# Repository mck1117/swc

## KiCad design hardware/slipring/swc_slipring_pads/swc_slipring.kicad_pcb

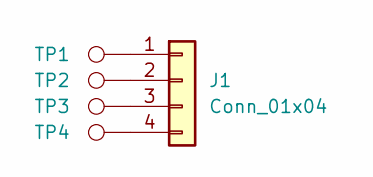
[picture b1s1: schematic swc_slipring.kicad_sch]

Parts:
J1: Conn_01x04; PinSocket_2x02_P2.54mm_Vertical_SMD
TP1, TP2, TP3, TP4: TestPoint; TestPoint_Pad_D3.0mm

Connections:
unnamed: J1.1, TP1.1
unnamed: J1.2, TP2.1
unnamed: J1.3, TP3.1
unnamed: J1.4, TP4.1

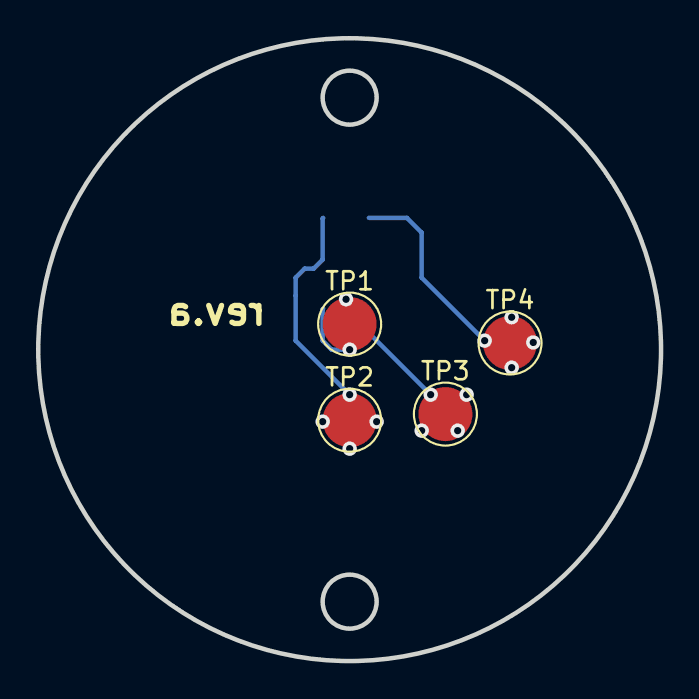
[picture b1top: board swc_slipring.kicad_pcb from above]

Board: 2 copper layers, 34.6 x 34.6 mm, 5 parts (1 on the bottom side), 4 nets.

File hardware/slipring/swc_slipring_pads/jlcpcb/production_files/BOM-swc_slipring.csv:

Comment,Designator,Footprint,LCSC
Conn_01x04,J1,PinSocket_2x02_P2.54mm_Vertical_SMD,
TestPoint,TP4,TestPoint_Pad_D3.0mm,
TestPoint,TP3,TestPoint_Pad_D3.0mm,
TestPoint,TP2,TestPoint_Pad_D3.0mm,
TestPoint,TP1,TestPoint_Pad_D3.0mm,

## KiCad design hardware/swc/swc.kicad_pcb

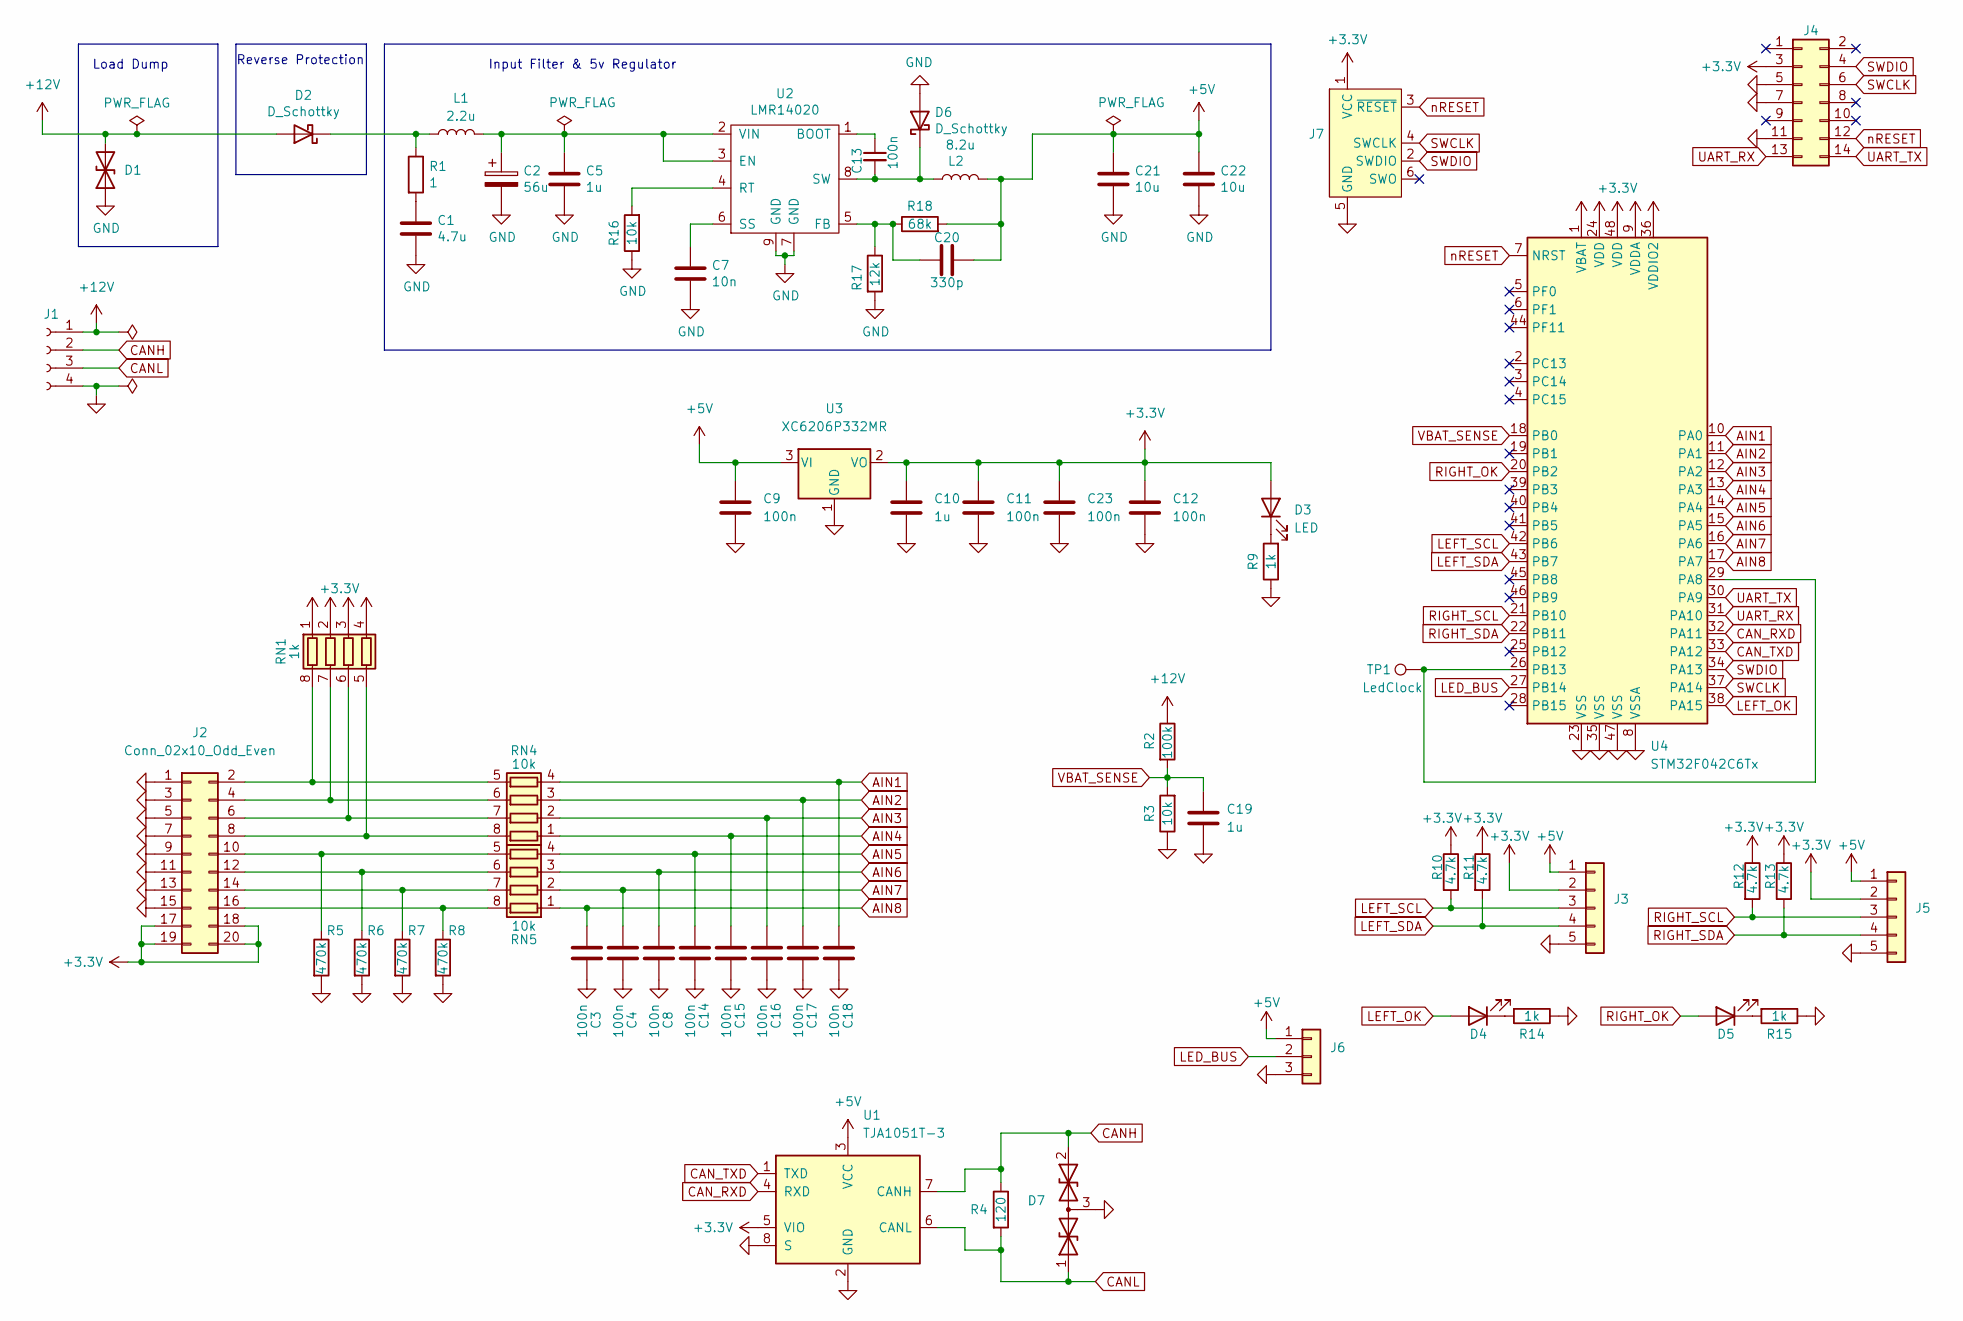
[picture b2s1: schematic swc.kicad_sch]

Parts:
C1: 4.7u; C_0603_1608Metric; LCSC C19666
C2: 56u; CP_Radial_D8.0mm_P3.50mm; LCSC N/A
C3, C4, C8, C9, C11, C12, C13, C14, C15, C16, C17, C18, C23: 100n; C_0603_1608Metric; LCSC C14663
C5, C10, C19: 1u; C_0603_1608Metric; LCSC C15849
C7: 10n; C_0402_1005Metric; LCSC_ext 0
C20: 330p; C_0402_1005Metric; LCSC C13533
C21, C22: 10u; C_1206_3216Metric; LCSC C13585
D1: SMBJ24CA; D_SMB; LCSC C78416
D2, D6: D_Schottky; D_SMA; LCSC C8678
D3, D4, D5: LED; LED_0603_1608Metric; LCSC C72041
D7: PESD1CAN; SOT-323_SC-70; LCSC C152727
J1: Conn_01x04_Female; JST_XH_B4B-XH-A_1x04_P2.50mm_Vertical
J2: Conn_02x10_Odd_Even; PinHeader_2x10_P2.00mm_Vertical
J3, J5: Conn_01x05; JST_XH_B5B-XH-A_1x05_P2.50mm_Vertical
J4: FTSH-107-01-F-DV-K; PinHeader_2x07_P1.27mm_Vertical_SMD
J6: Conn_01x03; JST_XH_B3B-XH-A_1x03_P2.50mm_Vertical
J7: Conn_ARM_SWD_TagConnect_TC2030-NL; Tag-Connect_TC2030-IDC-NL_2x03_P1.27mm_Vertical
L1: 2.2u; L_1210_3225Metric; LCSC C36828
L2: 8.2u; L_Bourns_SRN6045TA
R1: 1; R_0402_1005Metric; LCSC C25086
R2: 100k; R_0603_1608Metric; LCSC C25803
R3, R16: 10k; R_0603_1608Metric; LCSC C25804
R4: 120; R_0805_2012Metric; LCSC C17437
R5, R6, R7, R8: 470k; R_0402_1005Metric
R9, R14, R15: 1k; R_0603_1608Metric; LCSC C21190
R10, R11, R12, R13: 4.7k; R_0603_1608Metric
R17: 12k; R_0402_1005Metric; LCSC C25752
R18: 68k; R_0402_1005Metric; LCSC C36871
RN1: 1k; R_Array_Convex_4x0603
RN4, RN5: 10k; R_Array_Convex_4x0603; LCSC C29718
TP1: LedClock; TestPoint_Pad_1.5x1.5mm
U1: TJA1051T-3; SOIC-8_3.9x4.9mm_P1.27mm; LCSC C38695
U2: LMR14020; SOIC-8-1EP_3.9x4.9mm_P1.27mm_EP2.29x3mm; LCSC C187824
U3: XC6206P332MR; SOT-23; LCSC C5446
U4: STM32F042C6Tx; LQFP-48_7x7mm_P0.5mm; LCSC C88447

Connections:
+3V3: C10.1, C11.1, C12.1, C23.1, D3.2 (A), J2.17, J2.18, J2.19, J2.20, J3.2, J4.3, J5.2, J7.1 (VCC), R10.1, R11.1, R12.1, R13.1, RN1.1 (R1.1), RN1.2 (R2.1), RN1.3 (R3.1), RN1.4 (R4.1), U1.5 (VIO), U3.2 (VO), U4.1 (VBAT), U4.9 (VDDA), U4.24 (VDD), U4.36 (VDDIO2), U4.48 (VDD)
+5V: C9.1, C20.1, C21.1, C22.1, J3.1, J5.1, J6.1, L2.2, R18.2, U1.3 (VCC), U3.3 (VI)
+12V: D1.2 (A2), D2.2 (A), J1.1, R2.1
AIN1: C18.1, RN4.4 (R4.1), U4.10 (PA0)
AIN2: C17.1, RN4.3 (R3.1), U4.11 (PA1)
AIN3: C16.1, RN4.2 (R2.1), U4.12 (PA2)
AIN4: C15.1, RN4.1 (R1.1), U4.13 (PA3)
AIN5: C14.1, RN5.4 (R4.1), U4.14 (PA4)
AIN6: C8.1, RN5.3 (R3.1), U4.15 (PA5)
AIN7: C4.1, RN5.2 (R2.1), U4.16 (PA6)
AIN8: C3.1, RN5.1 (R1.1), U4.17 (PA7)
CANH: D7.2 (A2), J1.2, R4.1, U1.7 (CANH)
CANL: D7.1 (A1), J1.3, R4.2, U1.6 (CANL)
CAN_RXD: U1.4 (RXD), U4.32 (PA11)
CAN_TXD: U1.1 (TXD), U4.33 (PA12)
GND: C1.2, C2.2, C3.2, C4.2, C5.2, C7.2, C8.2, C9.2, C10.2, C11.2, C12.2, C14.2, C15.2, C16.2, C17.2, C18.2, C19.2, C21.2, C22.2, C23.2, D1.1 (A1), D6.2 (A), D7.3 (common), J1.4, J2.1, J2.3, J2.5, J2.7, J2.9, J2.11, J2.13, J2.15, J3.5, J4.5, J4.7, J4.11, J5.5, J6.3, J7.5 (GND), R3.1, R5.2, R6.2, R7.2, R8.2, R9.1, R14.1, R15.1, R16.1, R17.2, U1.2 (GND), U1.8 (S), U2.7 (GND), U2.9 (GND), U3.1 (GND), U4.8 (VSSA), U4.23 (VSS), U4.35 (VSS), U4.47 (VSS)
LED_BUS: J6.2, U4.27 (PB14)
LEFT_OK: D4.2 (A), U4.38 (PA15)
LEFT_SCL: J3.3, R10.2, U4.42 (PB6)
LEFT_SDA: J3.4, R11.2, U4.43 (PB7)
unnamed: C1.1, R1.2
unnamed: C2.1, C5.1, L1.2, U2.2 (VIN), U2.3 (EN)
unnamed: C7.1, U2.6 (SS)
unnamed: C13.1, U2.1 (BOOT)
unnamed: C13.2, D6.1 (K), L2.1, U2.8 (SW)
unnamed: C20.2, R17.1, R18.1, U2.5 (FB)
unnamed: D2.1 (K), L1.1, R1.1
unnamed: D3.1 (K), R9.2
unnamed: D4.1 (K), R14.2
unnamed: D5.1 (K), R15.2
unnamed: J2.2, RN1.8 (R1.2), RN4.5 (R4.2)
unnamed: J2.4, RN1.7 (R2.2), RN4.6 (R3.2)
unnamed: J2.6, RN1.6 (R3.2), RN4.7 (R2.2)
unnamed: J2.8, RN1.5 (R4.2), RN4.8 (R1.2)
unnamed: J2.10, R5.1, RN5.5 (R4.2)
unnamed: J2.12, R6.1, RN5.6 (R3.2)
unnamed: J2.14, R7.1, RN5.7 (R2.2)
unnamed: J2.16, R8.1, RN5.8 (R1.2)
unnamed: R16.2, U2.4 (RT)
unnamed: TP1.1, U4.26 (PB13), U4.29 (PA8)
RIGHT_OK: D5.2 (A), U4.20 (PB2)
RIGHT_SCL: J5.3, R12.2, U4.21 (PB10)
RIGHT_SDA: J5.4, R13.2, U4.22 (PB11)
SWCLK: J4.6, J7.4 (SWCLK), U4.37 (PA14)
SWDIO: J4.4, J7.2 (SWDIO), U4.34 (PA13)
UART_RX: J4.13, U4.31 (PA10)
UART_TX: J4.14, U4.30 (PA9)
VBAT_SENSE: C19.1, R2.2, R3.2, U4.18 (PB0)
nRESET: J4.12, J7.3 (~RESET), U4.7 (NRST)

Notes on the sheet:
Input Filter & 5v Regulator
Load Dump
Reverse Protection

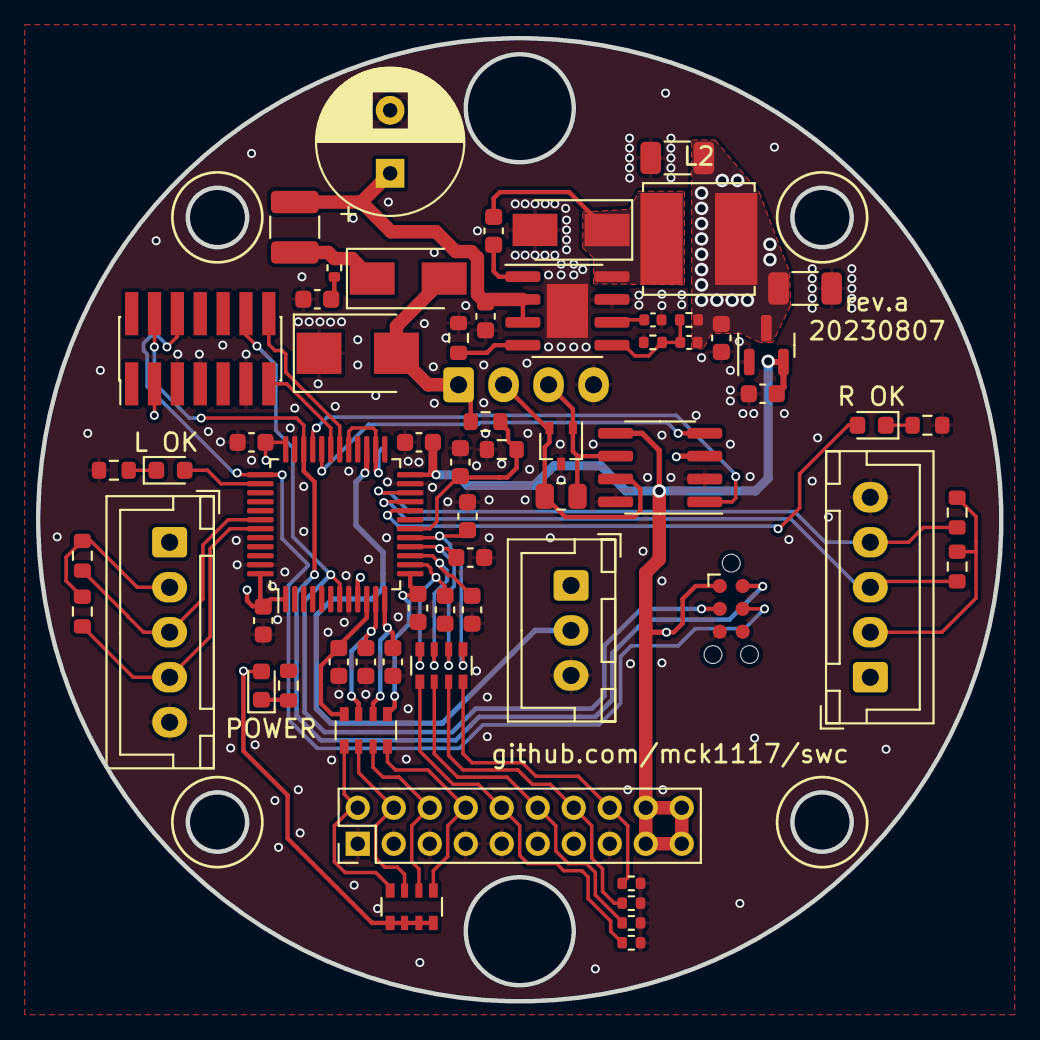
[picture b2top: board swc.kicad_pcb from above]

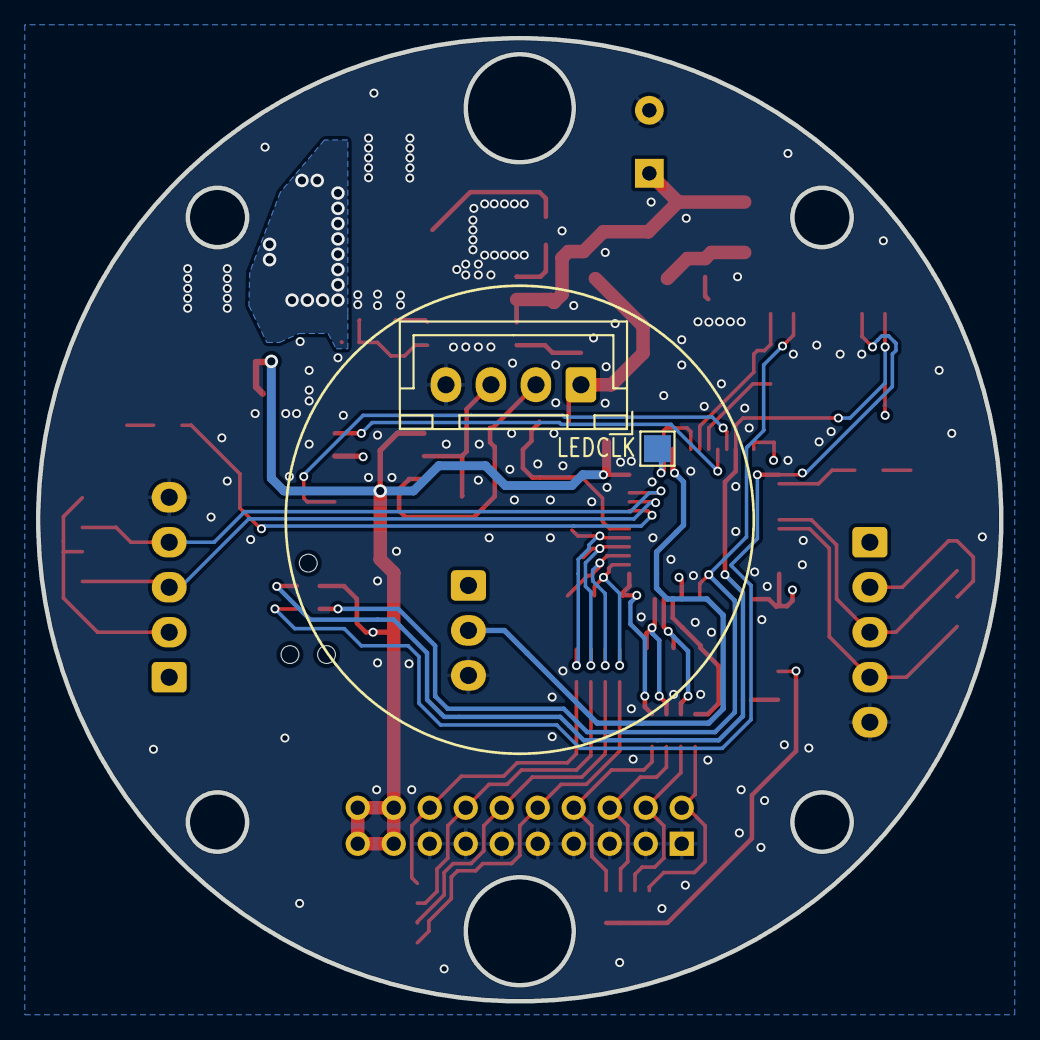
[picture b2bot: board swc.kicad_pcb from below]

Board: 4 copper layers, 53.5 x 53.5 mm, 64 parts (2 on the bottom side), 49 nets.

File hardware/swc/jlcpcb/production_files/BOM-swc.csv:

Comment,Designator,Footprint,LCSC
330p,C20,C_0402_1005Metric,C13533
10u,"C21,C22",C_1206_3216Metric,C13585
100n,"C11,C12,C13,C14,C15,C16,C17,C18,C23,C3,C4,C8,C9",C_0603_1608Metric,C14663
10n,C7,C_0402_1005Metric,C15195
PESD1CAN,D7,SOT-323_SC-70,C152727
1u,"C10,C19,C5",C_0603_1608Metric,C15849
120,R4,R_0805_2012Metric,C17437
LMR14020,U2,SOIC-8-1EP_3.9x4.9mm_P1.27mm_EP2.29x3mm,C187824
4.7u,C1,C_0603_1608Metric,C19666
1k,RN1,R_Array_Convex_4x0603,C20197
1k,"R14,R15,R9",R_0603_1608Metric,C21190
4.7k,"R10,R11,R12,R13",R_0603_1608Metric,C23162
1,R1,R_0402_1005Metric,C25086
12k,R17,R_0402_1005Metric,C25752
470k,"R5,R6,R7,R8",R_0402_1005Metric,C25790
100k,R2,R_0603_1608Metric,C25803
10k,"R16,R3",R_0603_1608Metric,C25804
10k,"RN4,RN5",R_Array_Convex_4x0603,C29718
2.2u,L1,L_1210_3225Metric,C36828
68k,R18,R_0402_1005Metric,C36871
TJA1051T-3,U1,SOIC-8_3.9x4.9mm_P1.27mm,C38695
XC6206P332MR,U3,SOT-23,C5446
LED,"D3,D4,D5",LED_0603_1608Metric,C72041
SMBJ24CA,D1,D_SMB,C78416
D_Schottky,"D2,D6",D_SMA,C8678
STM32F042C6Tx,U4,LQFP-48_7x7mm_P0.5mm,C88447
56u,C2,CP_Radial_D8.0mm_P3.50mm,
LedClock,TP1,TestPoint_Pad_1.5x1.5mm,
Conn_ARM_SWD_TagConnect_TC2030-NL,J7,Tag-Connect_TC2030-IDC-NL_2x03_P1.27mm_Vertical,

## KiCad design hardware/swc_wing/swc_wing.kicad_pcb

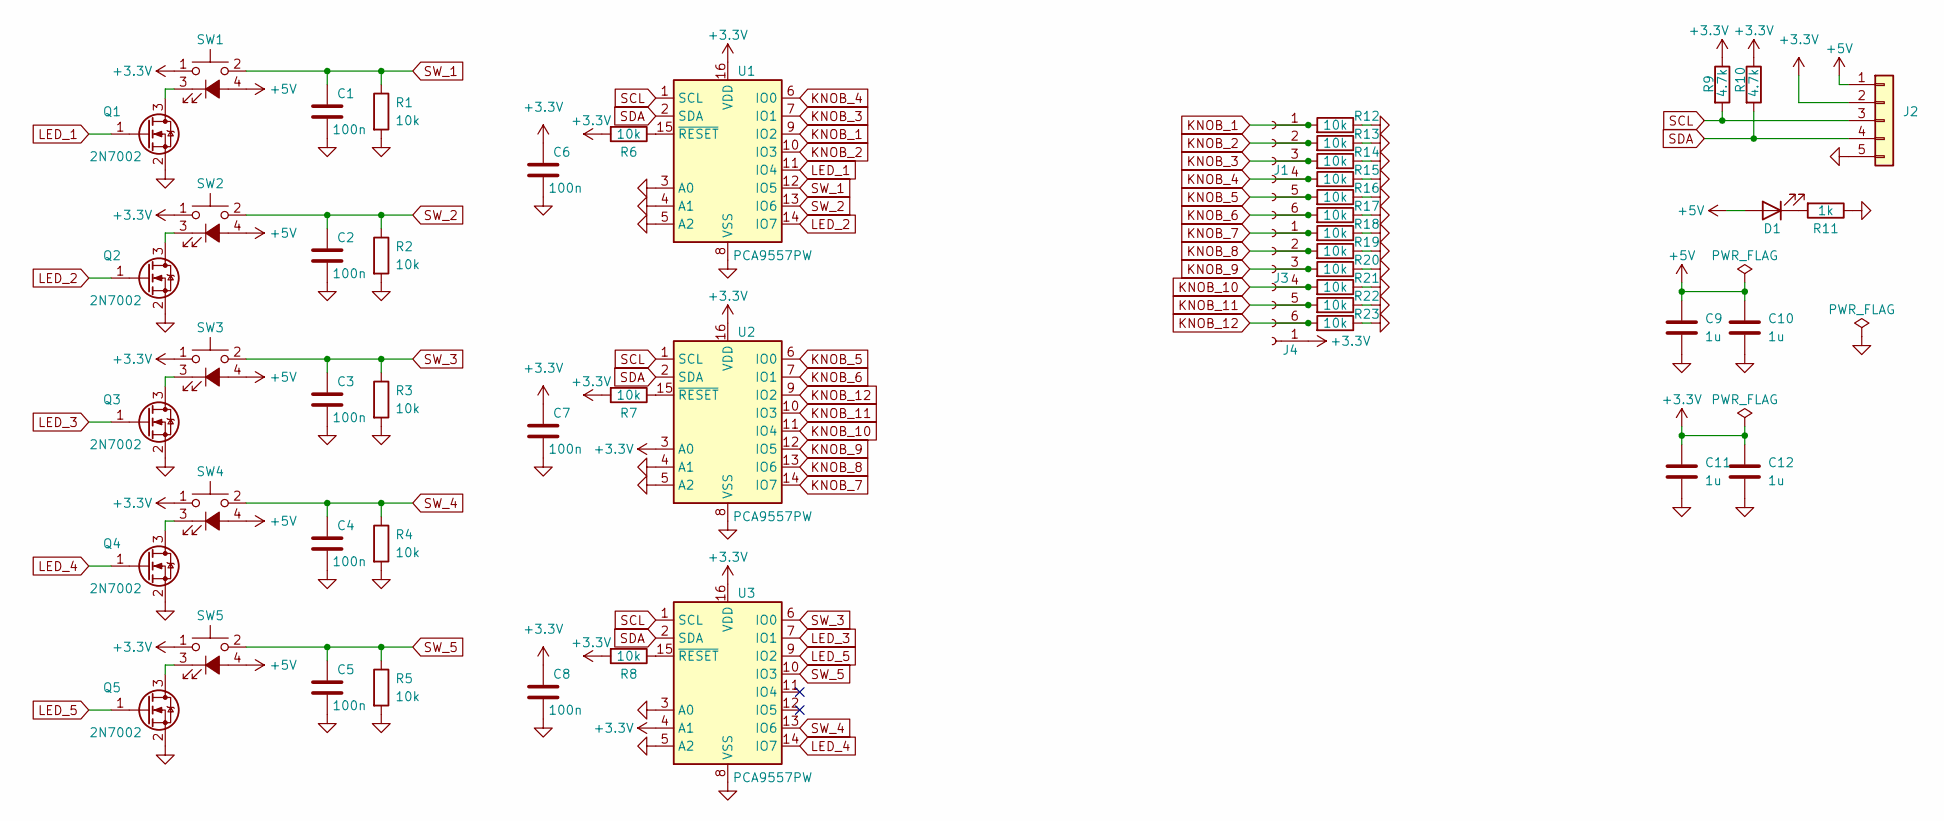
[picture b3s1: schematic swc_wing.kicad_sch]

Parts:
C1, C2, C3, C4, C5, C6, C7, C8: 100n; C_0603_1608Metric; LCSC C14663
C9, C10, C11, C12: 1u; C_0603_1608Metric; LCSC C15849
D1: LED; LED_0603_1608Metric; LCSC C72043
J1, J3: Conn_01x06_Female; PinHeader_1x06_P2.00mm_Vertical
J2: Conn_01x05; PinHeader_1x05_P2.54mm_Horizontal
J4: Conn_01x01_Female; PinHeader_1x01_P2.00mm_Vertical
Q1, Q2, Q3, Q4, Q5: 2N7002; SOT-23; LCSC C8545
R1, R2, R3, R4, R5, R6, R7, R8, R12, R13, R14, R15, R16, R17, R18, R19, R20, R21, R22, R23: 10k; R_0603_1608Metric; LCSC C25804
R9, R10: 4.7k; R_0603_1608Metric; LCSC C23162
R11: 1k; R_0603_1608Metric; LCSC C21190
SW1: SW_Push_LED; PinHeader_1x04_P2.54mm_Vertical
SW2, SW3, SW4, SW5: SW_Push_LED; FL12Lx5
U1, U2, U3: PCA9557PW; TSSOP-16_4.4x5mm_P0.65mm; LCSC C201547

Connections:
+3.3V: C6.1, C7.1, C8.1, C11.1, C12.1, J2.2, J4.1, R6.2, R7.2, R8.2, R9.1, R10.1, SW1.1, SW2.1, SW3.1, SW4.1, SW5.1, U1.16 (VDD), U2.3 (A0), U2.16 (VDD), U3.4 (A1), U3.16 (VDD)
+5V: C9.1, C10.1, D1.2 (A), J2.1, SW1.4 (A), SW2.4 (A), SW3.4 (A), SW4.4 (A), SW5.4 (A)
GND: C1.2, C2.2, C3.2, C4.2, C5.2, C6.2, C7.2, C8.2, C9.2, C10.2, C11.2, C12.2, J2.5, Q1.2 (S), Q2.2 (S), Q3.2 (S), Q4.2 (S), Q5.2 (S), R1.2, R2.2, R3.2, R4.2, R5.2, R11.1, R12.1, R13.1, R14.1, R15.1, R16.1, R17.1, R18.1, R19.1, R20.1, R21.1, R22.1, R23.1, U1.3 (A0), U1.4 (A1), U1.5 (A2), U1.8 (VSS), U2.4 (A1), U2.5 (A2), U2.8 (VSS), U3.3 (A0), U3.5 (A2), U3.8 (VSS)
KNOB_1: J1.1, R12.2, U1.9 (IO2)
KNOB_2: J1.2, R13.2, U1.10 (IO3)
KNOB_3: J1.3, R14.2, U1.7 (IO1)
KNOB_4: J1.4, R15.2, U1.6 (IO0)
KNOB_5: J1.5, R16.2, U2.6 (IO0)
KNOB_6: J1.6, R17.2, U2.7 (IO1)
KNOB_7: J3.1, R18.2, U2.14 (IO7)
KNOB_8: J3.2, R19.2, U2.13 (IO6)
KNOB_9: J3.3, R20.2, U2.12 (IO5)
KNOB_10: J3.4, R21.2, U2.11 (IO4)
KNOB_11: J3.5, R22.2, U2.10 (IO3)
KNOB_12: J3.6, R23.2, U2.9 (IO2)
LED_1: Q1.1 (G), U1.11 (IO4)
LED_2: Q2.1 (G), U1.14 (IO7)
LED_3: Q3.1 (G), U3.7 (IO1)
LED_4: Q4.1 (G), U3.14 (IO7)
LED_5: Q5.1 (G), U3.9 (IO2)
unnamed: D1.1 (K), R11.2
unnamed: Q1.3 (D), SW1.3 (K)
unnamed: Q2.3 (D), SW2.3 (K)
unnamed: Q3.3 (D), SW3.3 (K)
unnamed: Q4.3 (D), SW4.3 (K)
unnamed: Q5.3 (D), SW5.3 (K)
unnamed: R6.1, U1.15 (~RESET)
unnamed: R7.1, U2.15 (~RESET)
unnamed: R8.1, U3.15 (~RESET)
SCL: J2.3, R9.2, U1.1 (SCL), U2.1 (SCL), U3.1 (SCL)
SDA: J2.4, R10.2, U1.2 (SDA), U2.2 (SDA), U3.2 (SDA)
SW_1: C1.1, R1.1, SW1.2, U1.12 (IO5)
SW_2: C2.1, R2.1, SW2.2, U1.13 (IO6)
SW_3: C3.1, R3.1, SW3.2, U3.6 (IO0)
SW_4: C4.1, R4.1, SW4.2, U3.13 (IO6)
SW_5: C5.1, R5.1, SW5.2, U3.10 (IO3)

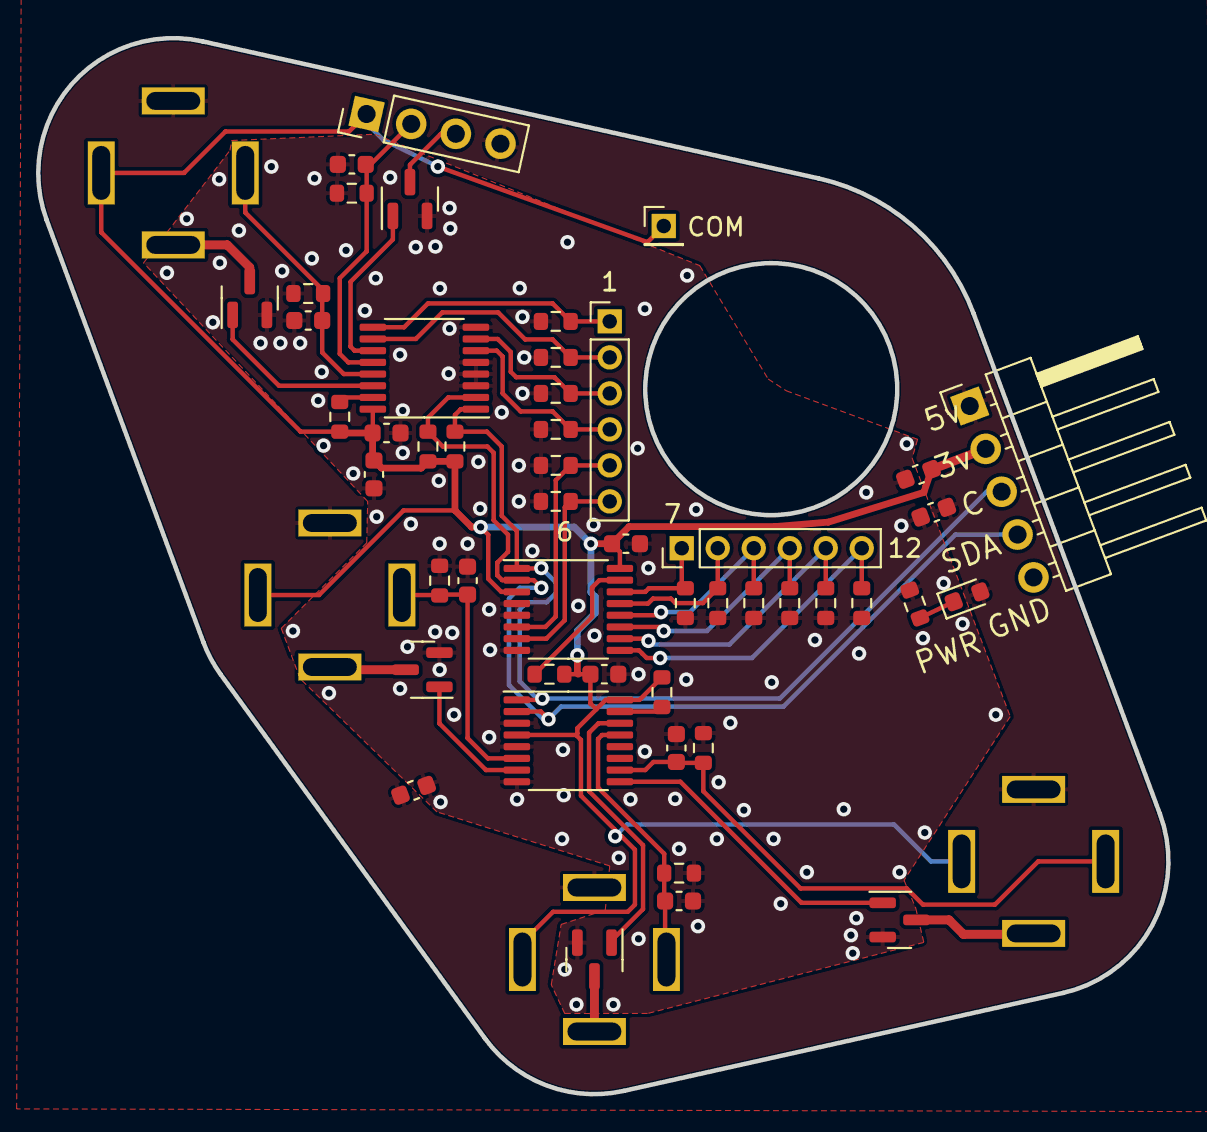
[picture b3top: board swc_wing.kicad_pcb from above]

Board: 2 copper layers, 62.8 x 58.7 mm, 53 parts (0 on the bottom side), 36 nets.

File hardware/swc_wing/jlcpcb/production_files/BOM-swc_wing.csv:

Comment,Designator,Footprint,LCSC
100n,"C1,C2,C3,C4,C5,C6,C7,C8",C_0603_1608Metric,C14663
1u,"C10,C11,C12,C9",C_0603_1608Metric,C15849
PCA9557PW,"U1,U2,U3",TSSOP-16_4.4x5mm_P0.65mm,C201547
1k,R11,R_0603_1608Metric,C21190
4.7k,"R10,R9",R_0603_1608Metric,C23162
10k,"R1,R12,R13,R14,R15,R16,R17,R18,R19,R2,R20,R21,R22,R23,R3,R4,R5,R6,R7,R8",R_0603_1608Metric,C25804
LED,D1,LED_0603_1608Metric,C72043
2N7002,"Q1,Q2,Q3,Q4,Q5",SOT-23,C8545
Conn_01x05,J2,PinHeader_1x05_P2.54mm_Horizontal,
SW_Push_LED,SW2,FL12Lx5,
Conn_01x01_Female,J4,PinHeader_1x01_P2.00mm_Vertical,
SW_Push_LED,SW1,PinHeader_1x04_P2.54mm_Vertical,
Conn_01x06_Female,J1,PinHeader_1x06_P2.00mm_Vertical,
SW_Push_LED,SW3,FL12Lx5,
SW_Push_LED,SW4,FL12Lx5,
SW_Push_LED,SW5,FL12Lx5,
Conn_01x06_Female,J3,PinHeader_1x06_P2.00mm_Vertical,

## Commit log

2023-08-07 gitignore
2023-08-07 chibios
2023-08-07 stub firmware
2023-08-07 narrow gitignores
2023-08-07 main board
2023-08-07 side board
2023-08-07 mcu features and clocking
2023-08-07 mcu features
2023-08-07 ci, because why not?
2023-08-07 missing lcsc
2023-08-07 close to final main board
2023-08-07 3.3v-ify wing
2023-08-07 gitignore wing, jlc db
2023-08-07 wing tweaks
2023-08-07 wing drc
2023-08-07 wing production files
2023-08-07 main board export
2023-08-07 rotation
2023-08-08 slip rings
2023-08-08 init CAN
2023-08-16 status LEDs go blinky
2023-08-16 hard fault handler
2023-08-16 sleep while idle
2023-08-16 bit banged i2c
2023-08-16 debug config
2023-08-16 leds reflect aliveness
2023-08-16 mirror buttons to LEDs
2023-08-16 auto reinit
2023-08-16 bitrate
2023-08-16 stub knob
2023-08-16 can transmit
2023-08-17 init can pins
2024-02-03 optimize for speed
2024-04-02 can tx, startup animation, dimming
2024-04-12 1mbit CAN
2024-04-13 embiggen stacks
2024-04-13 buttons and leds work over CAN!
